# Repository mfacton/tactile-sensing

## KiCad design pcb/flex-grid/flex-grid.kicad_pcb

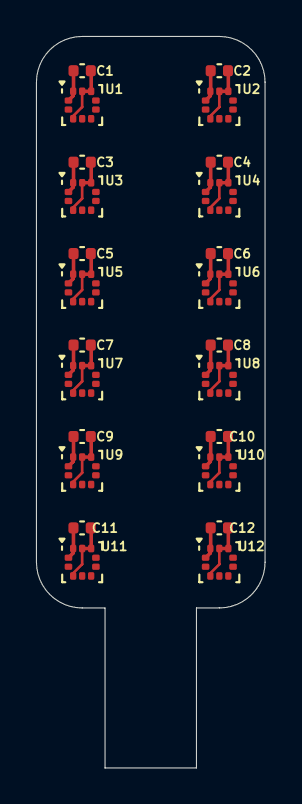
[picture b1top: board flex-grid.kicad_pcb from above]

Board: 2 copper layers, 12.7 x 40.6 mm, 24 parts (0 on the bottom side), 4 nets.

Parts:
C1, C2, C3, C4, C5, C6, C7, C8, C9, C10, C11, C12: 1u; C_0402_1005Metric
U1, U2, U3, U4, U5, U6, U7, U8, U9, U10, U11, U12: LPS22HB; ST_HLGA-10_2x2mm_P0.5mm_LayoutBorder3x2y

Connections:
/SCK: U1.2 (SCL), U2.2 (SCL), U3.2 (SCL), U4.2 (SCL), U5.2 (SCL), U6.2 (SCL), U7.2 (SCL), U8.2 (SCL), U9.2 (SCL), U10.2 (SCL), U11.2 (SCL), U12.2 (SCL)
/SDIO: U1.4 (SDA), U2.4 (SDA), U3.4 (SDA), U4.4 (SDA), U5.4 (SDA), U6.4 (SDA), U7.4 (SDA), U8.4 (SDA), U9.4 (SDA), U10.4 (SDA), U11.4 (SDA), U12.4 (SDA)
GND: C1.2, C2.2, C3.2, C4.2, C5.2, C6.2, C7.2, C8.2, C9.2, C10.2, C11.2, C12.2, U1.3 (RES), U1.8 (GND), U1.9 (GND), U2.3 (RES), U2.8 (GND), U2.9 (GND), U3.3 (RES), U3.8 (GND), U3.9 (GND), U4.3 (RES), U4.8 (GND), U4.9 (GND), U5.3 (RES), U5.8 (GND), U5.9 (GND), U6.3 (RES), U6.8 (GND), U6.9 (GND), U7.3 (RES), U7.8 (GND), U7.9 (GND), U8.3 (RES), U8.8 (GND), U8.9 (GND), U9.3 (RES), U9.8 (GND), U9.9 (GND), U10.3 (RES), U10.8 (GND), U10.9 (GND), U11.3 (RES), U11.8 (GND), U11.9 (GND), U12.3 (RES), U12.8 (GND), U12.9 (GND)
VDD: C1.1, C2.1, C3.1, C4.1, C5.1, C6.1, C7.1, C8.1, C9.1, C10.1, C11.1, C12.1, U1.1 (Vdd_IO), U1.10 (VDD), U2.1 (Vdd_IO), U2.10 (VDD), U3.1 (Vdd_IO), U3.10 (VDD), U4.1 (Vdd_IO), U4.10 (VDD), U5.1 (Vdd_IO), U5.10 (VDD), U6.1 (Vdd_IO), U6.10 (VDD), U7.1 (Vdd_IO), U7.10 (VDD), U8.1 (Vdd_IO), U8.10 (VDD), U9.1 (Vdd_IO), U9.10 (VDD), U10.1 (Vdd_IO), U10.10 (VDD), U11.1 (Vdd_IO), U11.10 (VDD), U12.1 (Vdd_IO), U12.10 (VDD)

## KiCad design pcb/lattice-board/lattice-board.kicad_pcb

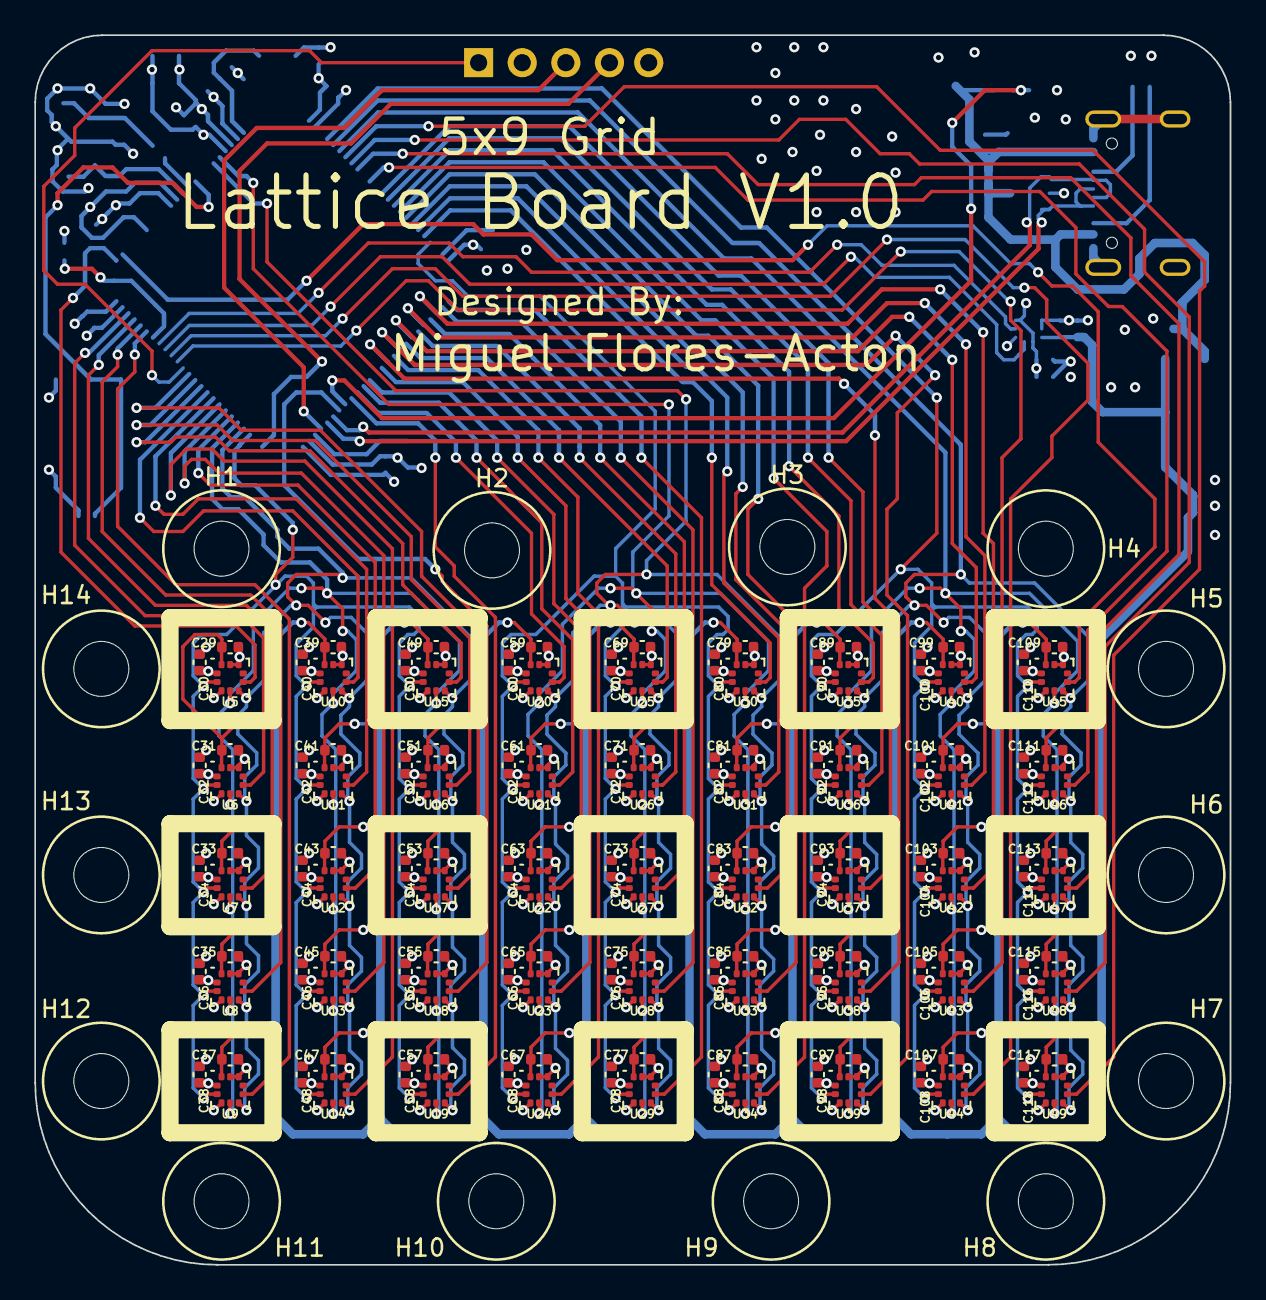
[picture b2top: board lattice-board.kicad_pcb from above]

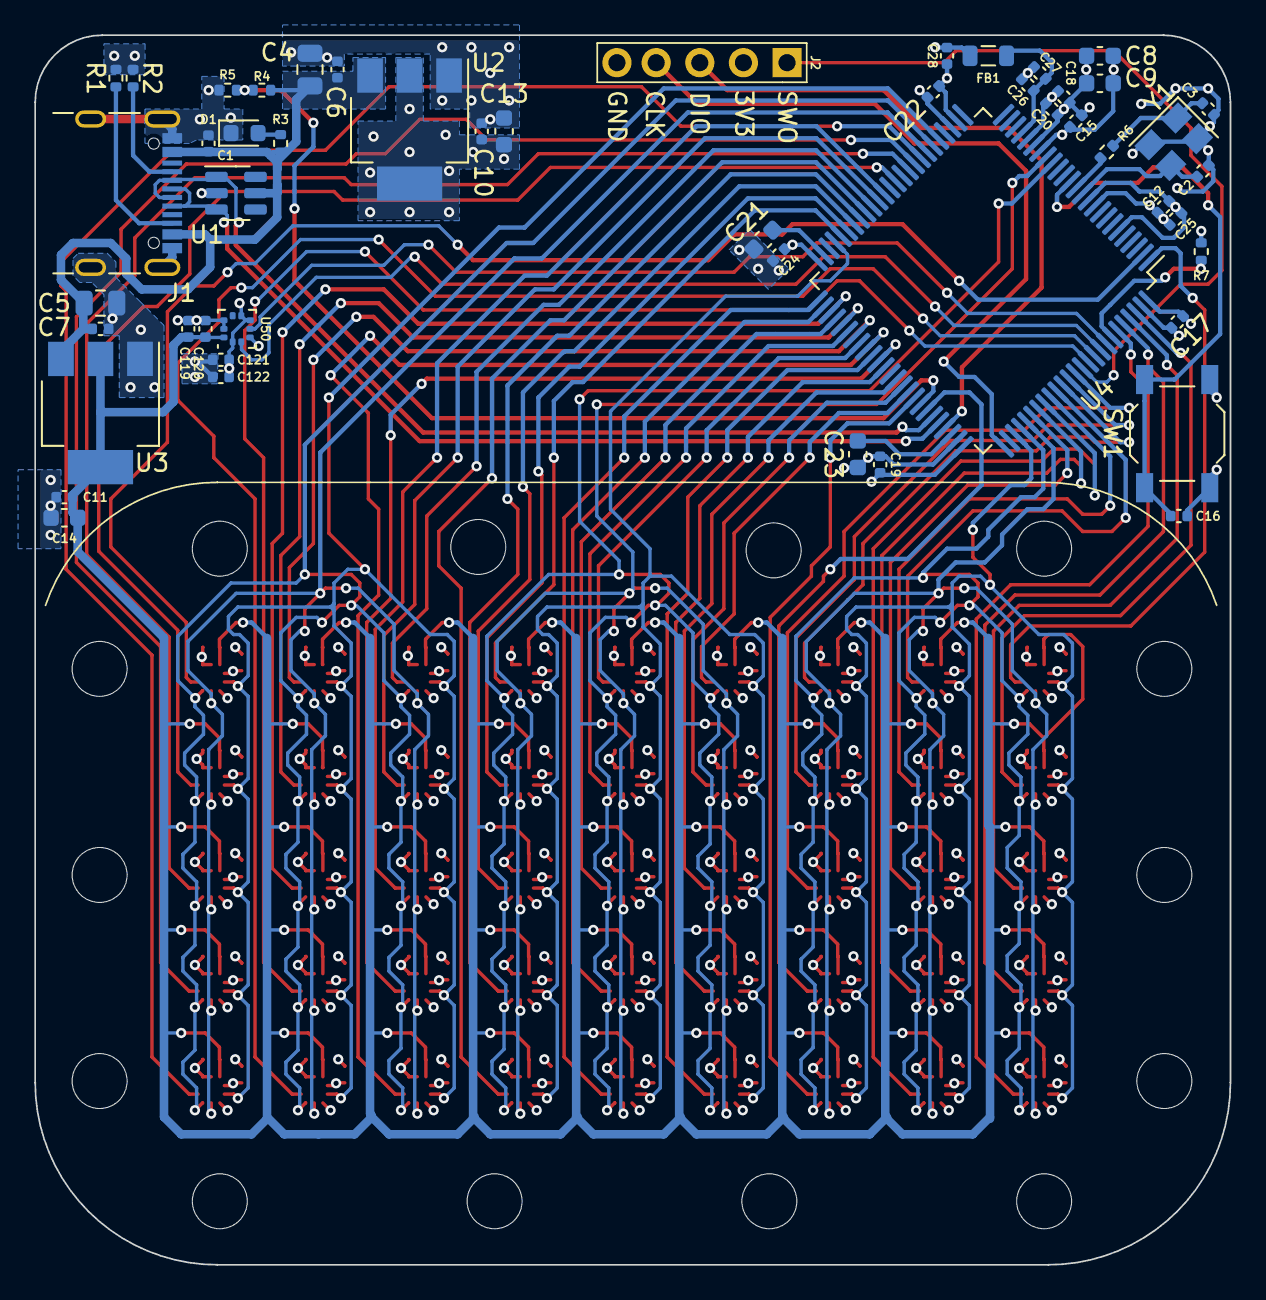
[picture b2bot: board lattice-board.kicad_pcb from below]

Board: 4 copper layers, 69.6 x 71.6 mm, 199 parts (50 on the bottom side), 77 nets.

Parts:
C1, C18, C27, C28: 1u; C_0402_1005Metric
C2, C3: 10p; C_0402_1005Metric
C4, C5: 22u; C_0805_2012Metric
C6, C7, C10, C11, C12, C15, C16, C17, C19, C20, C22, C24, C25, C26, C29, C30, C31, C32, C33, C34, C35, C36, C37, C38, C39, C40, C41, C42, C43, C44, C45, C46, C47, C48, C49, C50, C51, C52, C53, C54, C55, C56, C57, C58, C59, C60, C61, C62, C63, C64, C65, C66, C67, C68, C69, C70, C71, C72, C73, C74, C75, C76, C77, C78, C79, C80, C81, C82, C83, C84, C85, C86, C87, C88, C89, C90, C91, C92, C93, C94, C95, C96, C97, C98, C99, C100, C101, C102, C103, C104, C105, C106, C107, C108, C109, C110, C111, C112, C113, C114, C115, C116, C117, C118, C120, C121: 100n; C_0402_1005Metric
C8, C9, C21, C23: 2.2u; C_0603_1608Metric
C13, C14: 22u; C_0603_1608Metric
C119, C122: 4u7; C_0402_1005Metric
D1: LED; LED_0603_1608Metric
FB1: FerriteBead; L_0805_2012Metric
H1, H2, H3, H4, H5, H6, H7, H8, H9, H10, H11, H12, H13, H14: MountingHole; MountingHole_3.2mm_M3
J1: USB_C_Receptacle_USB2.0; USB_C_Receptacle_GCT_USB4105-xx-A_16P_TopMnt_Horizontal
J2: Conn_01x05_Pin; Conn_Header_P5-2.54
R1, R2: 5k1; R_0402_1005Metric
R3, R6: 510; R_0402_1005Metric
R4, R5, R7: 10k; R_0402_1005Metric
SW1: SW_Push; SW_SPST_TL3342
U1: SRV05-4; SOT-23-6
U2, U3: AMS1117-3.3; SOT-223-3_TabPin2
U4: STM32F407VETx; LQFP-100_14x14mm_P0.5mm
U5, U6, U7, U8, U9, U10, U11, U12, U13, U14, U15, U16, U17, U18, U19, U20, U21, U22, U23, U24, U25, U26, U27, U28, U29, U30, U31, U32, U33, U34, U35, U36, U37, U38, U39, U40, U41, U42, U43, U44, U45, U46, U47, U48, U49, U50: LPS22HB; ST_HLGA-10_2x2mm_P0.5mm_LayoutBorder3x2y
Y1: 16MHz; Crystal_SMD_3225-4Pin_3.2x2.5mm

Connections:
+3.3VA: C26.1, C27.1, FB1.1, U4.22 (VDDA)
/BOOT0: R7.1, U4.94 (BOOT0)
/CSnA1: U4.1 (PE2), U5.6 (~CS)
/CSnA2: U4.98 (PE1), U6.6 (~CS)
/CSnA3: U4.97 (PE0), U7.6 (~CS)
/CSnA4: U4.96 (PB9), U8.6 (~CS)
/CSnA5: U4.95 (PB8), U9.6 (~CS)
/CSnA6: U4.85 (PD4), U10.6 (~CS)
/CSnA7: U4.84 (PD3), U11.6 (~CS)
/CSnA8: U4.81 (PD0), U12.6 (~CS)
/CSnA9: U4.82 (PD1), U13.6 (~CS)
/CSnA10: U4.83 (PD2), U14.6 (~CS)
/CSnA11: U4.86 (PD5), U15.6 (~CS)
/CSnA12: U4.87 (PD6), U16.6 (~CS)
/CSnA13: U4.88 (PD7), U17.6 (~CS)
/CSnA14: U4.69 (PA10), U18.6 (~CS)
/CSnA15: U4.67 (PA8), U19.6 (~CS)
/CSnB1: U4.66 (PC9), U20.6 (~CS)
/CSnB2: U4.65 (PC8), U21.6 (~CS)
/CSnB3: U4.64 (PC7), U22.6 (~CS)
/CSnB4: U4.62 (PD15), U23.6 (~CS)
/CSnB5: U4.60 (PD13), U24.6 (~CS)
/CSnB6: U4.58 (PD11), U25.6 (~CS)
/CSnB7: U4.56 (PD9), U26.6 (~CS)
/CSnB8: U4.54 (PB15), U27.6 (~CS)
/CSnB9: U4.52 (PB13), U28.6 (~CS)
/CSnB10: U4.51 (PB12), U29.6 (~CS)
/CSnB11: U4.46 (PE15), U30.6 (~CS)
/CSnB12: U4.45 (PE14), U31.6 (~CS)
/CSnB13: U4.44 (PE13), U32.6 (~CS)
/CSnB14: U4.43 (PE12), U33.6 (~CS)
/CSnB15: U4.42 (PE11), U34.6 (~CS)
/CSnC1: U4.41 (PE10), U35.6 (~CS)
/CSnC2: U4.40 (PE9), U36.6 (~CS)
/CSnC3: U4.39 (PE8), U37.6 (~CS)
/CSnC4: U4.61 (PD14), U38.6 (~CS)
/CSnC5: U4.59 (PD12), U39.6 (~CS)
/CSnC6: U4.57 (PD10), U40.6 (~CS)
/CSnC7: U4.55 (PD8), U41.6 (~CS)
/CSnC8: U4.53 (PB14), U42.6 (~CS)
/CSnC9: U4.90 (PB4), U43.6 (~CS)
/CSnC10: U4.91 (PB5), U44.6 (~CS)
/CSnC11: U4.2 (PE3), U45.6 (~CS)
/CSnC12: U4.37 (PB2), U46.6 (~CS)
/CSnC13: U4.35 (PB0), U47.6 (~CS)
/CSnC14: U4.34 (PC5), U48.6 (~CS)
/CSnC15: U4.33 (PC4), U49.6 (~CS)
/NRST: C16.1, SW1.1, U4.14 (NRST)
/OSCIN: C2.2, U4.12 (PH0), Y1.3
/OSCLO: C3.2, R6.1, Y1.1
/OSCOUT: R6.2, U4.13 (PH1)
/SCKA: U4.78 (PC10), U5.2 (SCL), U6.2 (SCL), U7.2 (SCL), U8.2 (SCL), U9.2 (SCL), U10.2 (SCL), U11.2 (SCL), U12.2 (SCL), U13.2 (SCL), U14.2 (SCL), U15.2 (SCL), U16.2 (SCL), U17.2 (SCL), U18.2 (SCL), U19.2 (SCL)
/SCKB: U4.47 (PB10), U20.2 (SCL), U21.2 (SCL), U22.2 (SCL), U23.2 (SCL), U24.2 (SCL), U25.2 (SCL), U26.2 (SCL), U27.2 (SCL), U28.2 (SCL), U29.2 (SCL), U30.2 (SCL), U31.2 (SCL), U32.2 (SCL), U33.2 (SCL), U34.2 (SCL)
/SCKC: U4.30 (PA5), U35.2 (SCL), U36.2 (SCL), U37.2 (SCL), U38.2 (SCL), U39.2 (SCL), U40.2 (SCL), U41.2 (SCL), U42.2 (SCL), U43.2 (SCL), U44.2 (SCL), U45.2 (SCL), U46.2 (SCL), U47.2 (SCL), U48.2 (SCL), U49.2 (SCL)
/SCL1: U4.92 (PB6), U50.2 (SCL)
/SDA1: U4.93 (PB7), U50.4 (SDA)
/SDIA: U4.80 (PC12), U5.4 (SDA), U6.4 (SDA), U7.4 (SDA), U8.4 (SDA), U9.4 (SDA), U10.4 (SDA), U11.4 (SDA), U12.4 (SDA), U13.4 (SDA), U14.4 (SDA), U15.4 (SDA), U16.4 (SDA), U17.4 (SDA), U18.4 (SDA), U19.4 (SDA)
/SDIB: U4.18 (PC3), U20.4 (SDA), U21.4 (SDA), U22.4 (SDA), U23.4 (SDA), U24.4 (SDA), U25.4 (SDA), U26.4 (SDA), U27.4 (SDA), U28.4 (SDA), U29.4 (SDA), U30.4 (SDA), U31.4 (SDA), U32.4 (SDA), U33.4 (SDA), U34.4 (SDA)
/SDIC: U4.32 (PA7), U35.4 (SDA), U36.4 (SDA), U37.4 (SDA), U38.4 (SDA), U39.4 (SDA), U40.4 (SDA), U41.4 (SDA), U42.4 (SDA), U43.4 (SDA), U44.4 (SDA), U45.4 (SDA), U46.4 (SDA), U47.4 (SDA), U48.4 (SDA), U49.4 (SDA)
/SDOA: U4.79 (PC11), U5.5 (SA0), U6.5 (SA0), U7.5 (SA0), U8.5 (SA0), U9.5 (SA0), U10.5 (SA0), U11.5 (SA0), U12.5 (SA0), U13.5 (SA0), U14.5 (SA0), U15.5 (SA0), U16.5 (SA0), U17.5 (SA0), U18.5 (SA0), U19.5 (SA0)
/SDOB: U4.17 (PC2), U20.5 (SA0), U21.5 (SA0), U22.5 (SA0), U23.5 (SA0), U24.5 (SA0), U25.5 (SA0), U26.5 (SA0), U27.5 (SA0), U28.5 (SA0), U29.5 (SA0), U30.5 (SA0), U31.5 (SA0), U32.5 (SA0), U33.5 (SA0), U34.5 (SA0)
/SDOC: U4.31 (PA6), U35.5 (SA0), U36.5 (SA0), U37.5 (SA0), U38.5 (SA0), U39.5 (SA0), U40.5 (SA0), U41.5 (SA0), U42.5 (SA0), U43.5 (SA0), U44.5 (SA0), U45.5 (SA0), U46.5 (SA0), U47.5 (SA0), U48.5 (SA0), U49.5 (SA0)
/SNSBUS: R4.2, R5.1, U4.68 (PA9)
/SWCLK: J2.4, U4.76 (PA14)
/SWDIO: J2.3, U4.72 (PA13)
/SWO: J2.1, U4.89 (PB3)
/USB_D+: J1.A6 (D+), J1.B6 (D+), U1.3 (IO2), U4.71 (PA12)
/USB_D-: J1.A7 (D-), J1.B7 (D-), U1.1 (IO1), U4.70 (PA11)
/VBLED: D1.2 (A), R3.2
/VCAP1: C21.1, U4.49 (VCAP_1)
/VCAP2: C23.1, U4.73 (VCAP_2)
GND: C1.2, C2.1, C3.1, C4.2, C5.2, C6.2, C7.2, C8.2, C9.2, C10.2, C11.2, C12.2, C13.2, C14.2, C15.2, C16.2, C17.2, C18.2, C19.2, C20.2, C21.2, C22.2, C23.2, C24.2, C25.2, C26.2, C27.2, C28.2, C29.2, C30.2, C31.2, C32.2, C33.2, C34.2, C35.2, C36.2, C37.2, C38.2, C39.2, C40.2, C41.2, C42.2, C43.2, C44.2, C45.2, C46.2, C47.2, C48.2, C49.2, C50.2, C51.2, C52.2, C53.2, C54.2, C55.2, C56.2, C57.2, C58.2, C59.2, C60.2, C61.2, C62.2, C63.2, C64.2, C65.2, C66.2, C67.2, C68.2, C69.2, C70.2, C71.2, C72.2, C73.2, C74.2, C75.2, C76.2, C77.2, C78.2, C79.2, C80.2, C81.2, C82.2, C83.2, C84.2, C85.2, C86.2, C87.2, C88.2, C89.2, C90.2, C91.2, C92.2, C93.2, C94.2, C95.2, C96.2, C97.2, C98.2, C99.2, C100.2, C101.2, C102.2, C103.2, C104.2, C105.2, C106.2, C107.2, C108.2, C109.2, C110.2, C111.2, C112.2, C113.2, C114.2, C115.2, C116.2, C117.2, C118.2, C119.2, C120.2, C121.2, C122.2, D1.1 (K), J1.A1 (GND), J1.A12 (GND), J1.B1 (GND), J1.B12 (GND), J1.S1 (SHIELD), J2.5, R1.2, R2.2, R5.2, R7.2, SW1.2, U1.2 (VN), U2.1 (GND), U3.1 (GND), U4.10 (VSS), U4.20 (VSSA), U4.27 (VSS), U4.74 (VSS), U4.99 (VSS), U5.3 (RES), U5.8 (GND), U5.9 (GND), U6.3 (RES), U6.8 (GND), U6.9 (GND), U7.3 (RES), U7.8 (GND), U7.9 (GND), U8.3 (RES), U8.8 (GND), U8.9 (GND), U9.3 (RES), U9.8 (GND), U9.9 (GND), U10.3 (RES), U10.8 (GND), U10.9 (GND), U11.3 (RES), U11.8 (GND), U11.9 (GND), U12.3 (RES), U12.8 (GND), U12.9 (GND), U13.3 (RES), U13.8 (GND), U13.9 (GND), U14.3 (RES), U14.8 (GND), U14.9 (GND), U15.3 (RES), U15.8 (GND), U15.9 (GND), U16.3 (RES), U16.8 (GND), U16.9 (GND), U17.3 (RES), U17.8 (GND), U17.9 (GND), U18.3 (RES), U18.8 (GND), U18.9 (GND), U19.3 (RES), U19.8 (GND), U19.9 (GND), U20.3 (RES), U20.8 (GND), U20.9 (GND), U21.3 (RES), U21.8 (GND), U21.9 (GND), U22.3 (RES), U22.8 (GND), U22.9 (GND), U23.3 (RES), U23.8 (GND), U23.9 (GND), U24.3 (RES), U24.8 (GND), U24.9 (GND), U25.3 (RES), U25.8 (GND), U25.9 (GND), U26.3 (RES), U26.8 (GND), U26.9 (GND), U27.3 (RES), U27.8 (GND), U27.9 (GND), U28.3 (RES), U28.8 (GND), U28.9 (GND), U29.3 (RES), U29.8 (GND), U29.9 (GND), U30.3 (RES), U30.8 (GND), U30.9 (GND), U31.3 (RES), U31.8 (GND), U31.9 (GND), U32.3 (RES), U32.8 (GND), U32.9 (GND), U33.3 (RES), U33.8 (GND), U33.9 (GND), U34.3 (RES), U34.8 (GND), U34.9 (GND), U35.3 (RES), U35.8 (GND), U35.9 (GND), U36.3 (RES), U36.8 (GND), U36.9 (GND), U37.3 (RES), U37.8 (GND), U37.9 (GND), U38.3 (RES), U38.8 (GND), U38.9 (GND), U39.3 (RES), U39.8 (GND), U39.9 (GND), U40.3 (RES), U40.8 (GND), U40.9 (GND), U41.3 (RES), U41.8 (GND), U41.9 (GND), U42.3 (RES), U42.8 (GND), U42.9 (GND), U43.3 (RES), U43.8 (GND), U43.9 (GND), U44.3 (RES), U44.8 (GND), U44.9 (GND), U45.3 (RES), U45.8 (GND), U45.9 (GND), U46.3 (RES), U46.8 (GND), U46.9 (GND), U47.3 (RES), U47.8 (GND), U47.9 (GND), U48.3 (RES), U48.8 (GND), U48.9 (GND), U49.3 (RES), U49.8 (GND), U49.9 (GND), U50.3 (RES), U50.8 (GND), U50.9 (GND), Y1.2, Y1.4
unnamed: J1.A5 (CC1), R2.1
unnamed: J1.B5 (CC2), R1.1
VBUS: C1.1, C4.1, C5.1, C6.1, C7.1, J1.A4 (VBUS), J1.A9 (VBUS), J1.B4 (VBUS), J1.B9 (VBUS), R3.1, R4.1, U1.5 (VP), U2.3 (VI), U3.3 (VI)
VDD: C8.1, C9.1, C10.1, C12.1, C13.1, C15.1, C17.1, C18.1, C19.1, C20.1, C22.1, C24.1, C25.1, C28.1, C30.1, C32.1, C34.1, C36.1, C38.1, C40.1, C42.1, C44.1, C46.1, C48.1, C50.1, C52.1, C54.1, C56.1, C58.1, C60.1, C62.1, C64.1, C66.1, C68.1, C70.1, C72.1, C74.1, C76.1, C78.1, C80.1, C82.1, C84.1, C86.1, C88.1, C90.1, C92.1, C94.1, C96.1, C98.1, C100.1, C102.1, C104.1, C106.1, C108.1, C110.1, C112.1, C114.1, C116.1, C118.1, C121.1, C122.1, FB1.2, J2.2, U2.2 (VO), U4.6 (VBAT), U4.11 (VDD), U4.19 (VDD), U4.21 (VREF+), U4.28 (VDD), U4.50 (VDD), U4.75 (VDD), U4.100 (VDD), U5.1 (Vdd_IO), U6.1 (Vdd_IO), U7.1 (Vdd_IO), U8.1 (Vdd_IO), U9.1 (Vdd_IO), U10.1 (Vdd_IO), U11.1 (Vdd_IO), U12.1 (Vdd_IO), U13.1 (Vdd_IO), U14.1 (Vdd_IO), U15.1 (Vdd_IO), U16.1 (Vdd_IO), U17.1 (Vdd_IO), U18.1 (Vdd_IO), U19.1 (Vdd_IO), U20.1 (Vdd_IO), U21.1 (Vdd_IO), U22.1 (Vdd_IO), U23.1 (Vdd_IO), U24.1 (Vdd_IO), U25.1 (Vdd_IO), U26.1 (Vdd_IO), U27.1 (Vdd_IO), U28.1 (Vdd_IO), U29.1 (Vdd_IO), U30.1 (Vdd_IO), U31.1 (Vdd_IO), U32.1 (Vdd_IO), U33.1 (Vdd_IO), U34.1 (Vdd_IO), U35.1 (Vdd_IO), U36.1 (Vdd_IO), U37.1 (Vdd_IO), U38.1 (Vdd_IO), U39.1 (Vdd_IO), U40.1 (Vdd_IO), U41.1 (Vdd_IO), U42.1 (Vdd_IO), U43.1 (Vdd_IO), U44.1 (Vdd_IO), U45.1 (Vdd_IO), U46.1 (Vdd_IO), U47.1 (Vdd_IO), U48.1 (Vdd_IO), U49.1 (Vdd_IO), U50.1 (Vdd_IO), U50.5 (SA0), U50.6 (~CS)
VDDA: C11.1, C14.1, C29.1, C31.1, C33.1, C35.1, C37.1, C39.1, C41.1, C43.1, C45.1, C47.1, C49.1, C51.1, C53.1, C55.1, C57.1, C59.1, C61.1, C63.1, C65.1, C67.1, C69.1, C71.1, C73.1, C75.1, C77.1, C79.1, C81.1, C83.1, C85.1, C87.1, C89.1, C91.1, C93.1, C95.1, C97.1, C99.1, C101.1, C103.1, C105.1, C107.1, C109.1, C111.1, C113.1, C115.1, C117.1, C119.1, C120.1, U3.2 (VO), U5.10 (VDD), U6.10 (VDD), U7.10 (VDD), U8.10 (VDD), U9.10 (VDD), U10.10 (VDD), U11.10 (VDD), U12.10 (VDD), U13.10 (VDD), U14.10 (VDD), U15.10 (VDD), U16.10 (VDD), U17.10 (VDD), U18.10 (VDD), U19.10 (VDD), U20.10 (VDD), U21.10 (VDD), U22.10 (VDD), U23.10 (VDD), U24.10 (VDD), U25.10 (VDD), U26.10 (VDD), U27.10 (VDD), U28.10 (VDD), U29.10 (VDD), U30.10 (VDD), U31.10 (VDD), U32.10 (VDD), U33.10 (VDD), U34.10 (VDD), U35.10 (VDD), U36.10 (VDD), U37.10 (VDD), U38.10 (VDD), U39.10 (VDD), U40.10 (VDD), U41.10 (VDD), U42.10 (VDD), U43.10 (VDD), U44.10 (VDD), U45.10 (VDD), U46.10 (VDD), U47.10 (VDD), U48.10 (VDD), U49.10 (VDD), U50.10 (VDD)

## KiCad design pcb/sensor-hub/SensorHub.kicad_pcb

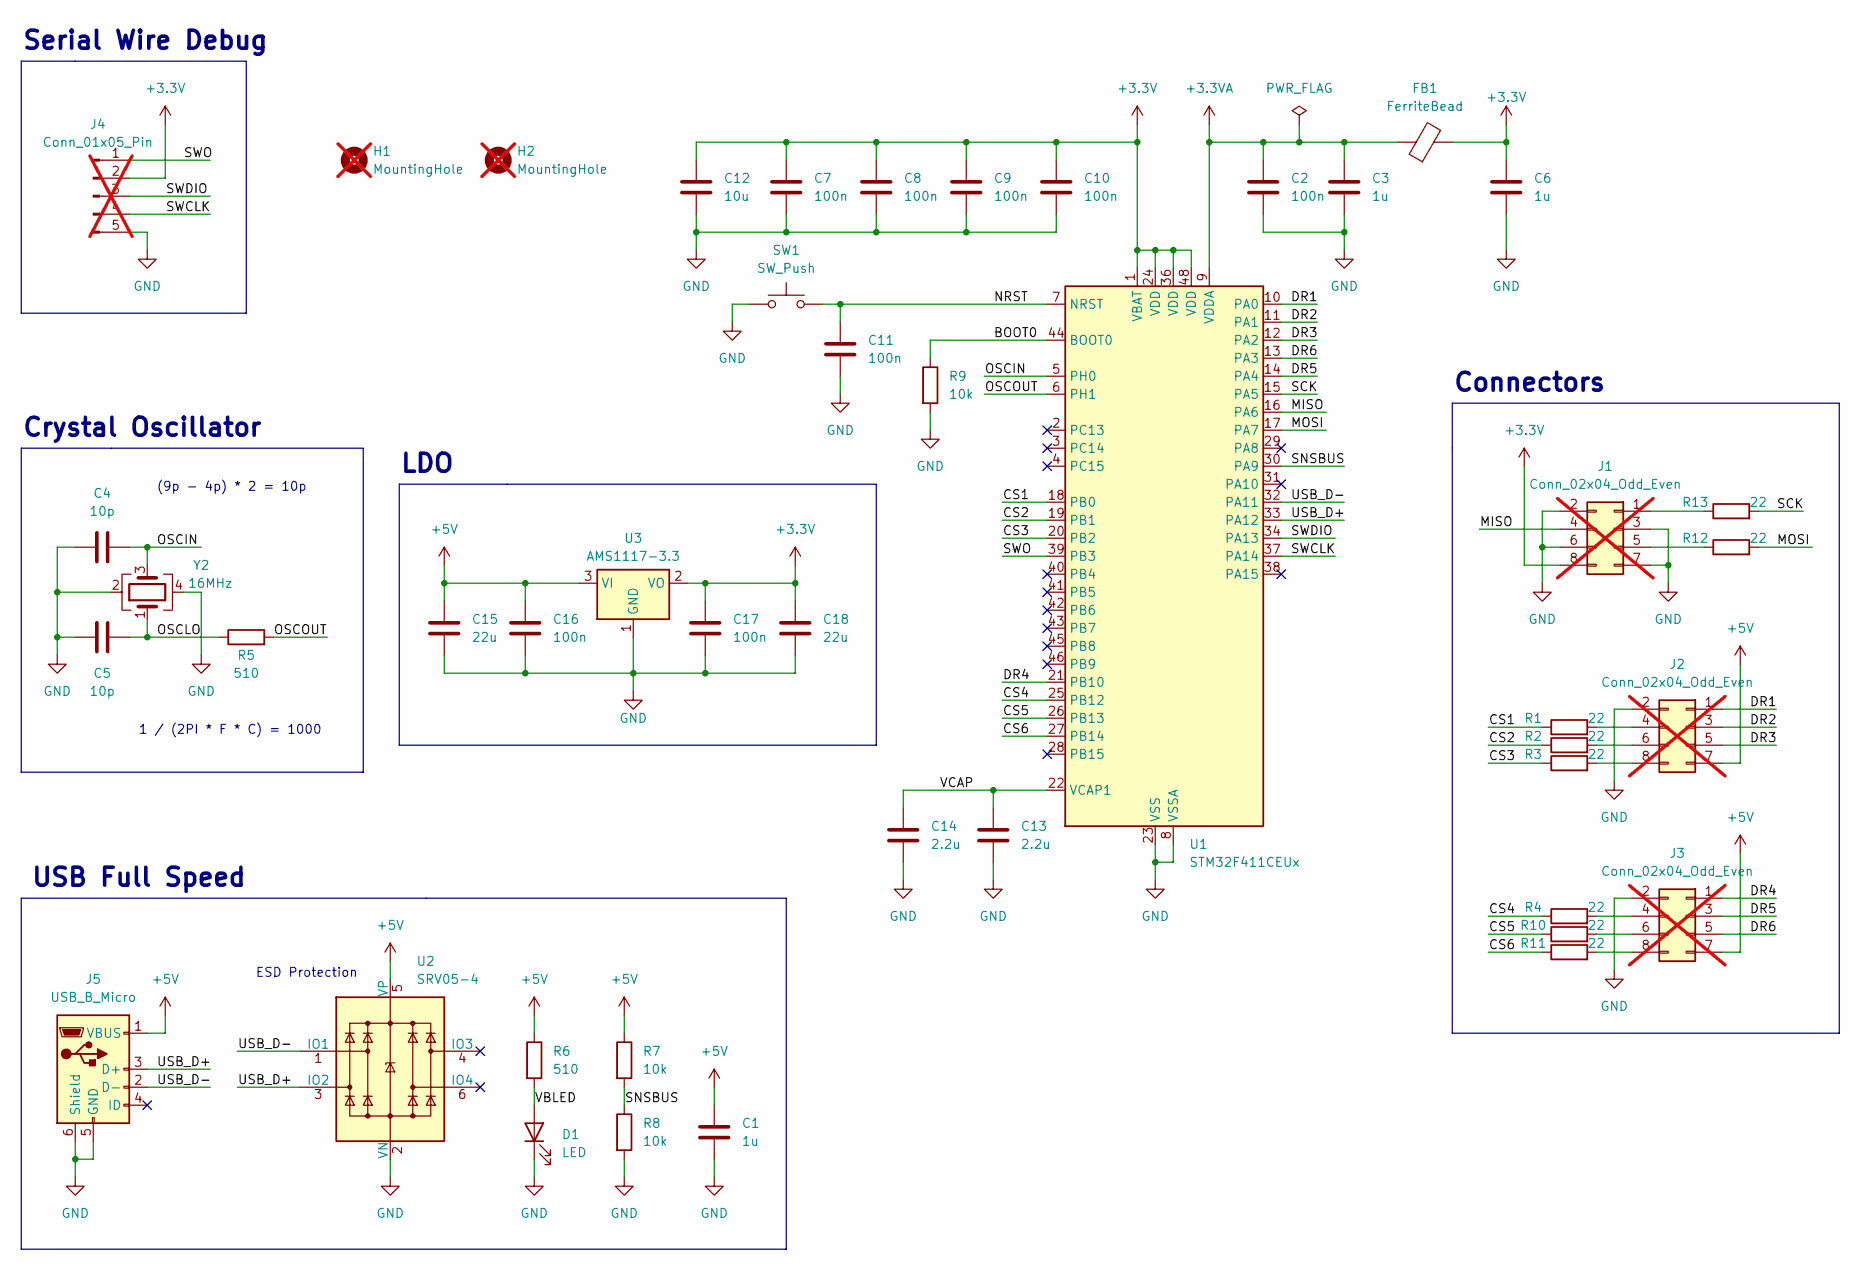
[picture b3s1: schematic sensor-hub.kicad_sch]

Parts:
C1, C3, C6: 1u; C_0402_1005Metric
C2, C7, C8, C9, C10, C11, C16, C17: 100n; C_0402_1005Metric
C4, C5: 10p; C_0402_1005Metric
C12: 10u; C_0603_1608Metric
C13, C14: 2.2u; C_0402_1005Metric
C15: 22u; C_0805_2012Metric
C18: 22u; C_0603_1608Metric
D1: LED; LED_0603_1608Metric
FB1: FerriteBead; L_0805_2012Metric; LCSC C32375
H1, H2: MountingHole; MountingHole_3.2mm_M3; not fitted
J1, J2, J3: Conn_02x04_Odd_Even; PinHeader_2x04_P2.54mm_Vertical; not fitted
J4: Conn_01x05_Pin; Conn_Header_P5-2.54; not fitted
J5: USB_B_Micro; USB_Micro-B_Molex-105017-0001; LCSC C668587
R1, R2, R3, R4, R10, R11, R12, R13: 22; R_0402_1005Metric
R5, R6: 510; R_0402_1005Metric
R7, R8, R9: 10k; R_0402_1005Metric
SW1: SW_Push; SW_SPST_TL3342
U1: STM32F411CEUx; QFN-48-1EP_7x7mm_P0.5mm_EP5.6x5.6mm; LCSC C60420
U2: SRV05-4; SOT-23-6; LCSC C7420376
U3: AMS1117-3.3; SOT-223-3_TabPin2; LCSC C6186
Y2: 16MHz; Crystal_SMD_3225-4Pin_3.2x2.5mm

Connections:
+3.3V: C6.1, C7.1, C8.1, C9.1, C10.1, C12.1, C17.1, C18.1, FB1.2, J1.8, J4.2, U1.1 (VBAT), U1.24 (VDD), U1.36 (VDD), U1.48 (VDD), U3.2 (VO)
+3.3VA: C2.1, C3.1, FB1.1, U1.9 (VDDA)
+5V: C1.1, C15.1, C16.1, J2.7, J3.7, J5.1 (VBUS), R6.1, R7.1, U2.5 (VP), U3.3 (VI)
/BOOT0: R9.1, U1.44 (BOOT0)
/CS1: R1.1, U1.18 (PB0)
/CS2: R2.1, U1.19 (PB1)
/CS3: R3.1, U1.20 (PB2)
/CS4: R4.1, U1.25 (PB12)
/CS5: R10.1, U1.26 (PB13)
/CS6: R11.1, U1.27 (PB14)
/DR1: J2.1, U1.10 (PA0)
/DR2: J2.3, U1.11 (PA1)
/DR3: J2.5, U1.12 (PA2)
/DR4: J3.1, U1.21 (PB10)
/DR5: J3.3, U1.14 (PA4)
/DR6: J3.5, U1.13 (PA3)
/MISO: J1.4, U1.16 (PA6)
/MOSI: R12.2, U1.17 (PA7)
/NRST: C11.1, SW1.1, U1.7 (NRST)
/OSCIN: C4.2, U1.5 (PH0), Y2.3
/OSCLO: C5.2, R5.1, Y2.1
/OSCOUT: R5.2, U1.6 (PH1)
/SCK: R13.2, U1.15 (PA5)
/SNSBUS: R7.2, R8.1, U1.30 (PA9)
/SWCLK: J4.4, U1.37 (PA14)
/SWDIO: J4.3, U1.34 (PA13)
/SWO: J4.1, U1.39 (PB3)
/USB_D+: J5.3 (D+), U1.33 (PA12), U2.3 (IO2)
/USB_D-: J5.2 (D-), U1.32 (PA11), U2.1 (IO1)
/VBLED: D1.2 (A), R6.2
/VCAP: C13.1, C14.1, U1.22 (VCAP1)
GND: C1.2, C2.2, C3.2, C4.1, C5.1, C6.2, C7.2, C8.2, C9.2, C10.2, C11.2, C12.2, C13.2, C14.2, C15.2, C16.2, C17.2, C18.2, D1.1 (K), J1.2, J1.3, J1.6, J1.7, J2.2, J3.2, J4.5, J5.5 (GND), J5.6 (Shield), R8.2, R9.2, SW1.2, U1.8 (VSSA), U1.23 (VSS), U1.35 (VSS), U1.47 (VSS), U1.49 (VSS), U2.2 (VN), U3.1 (GND), Y2.2, Y2.4
unnamed: J1.1, R13.1
unnamed: J1.5, R12.1
unnamed: J2.4, R1.2
unnamed: J2.6, R2.2
unnamed: J2.8, R3.2
unnamed: J3.4, R4.2
unnamed: J3.6, R10.2
unnamed: J3.8, R11.2

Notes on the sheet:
USB Full Speed
Connectors
ESD Protection
1 / (2PI * F * C) = 1000
Serial Wire Debug
LDO
Crystal Oscillator
(9p - 4p) * 2 = 10p

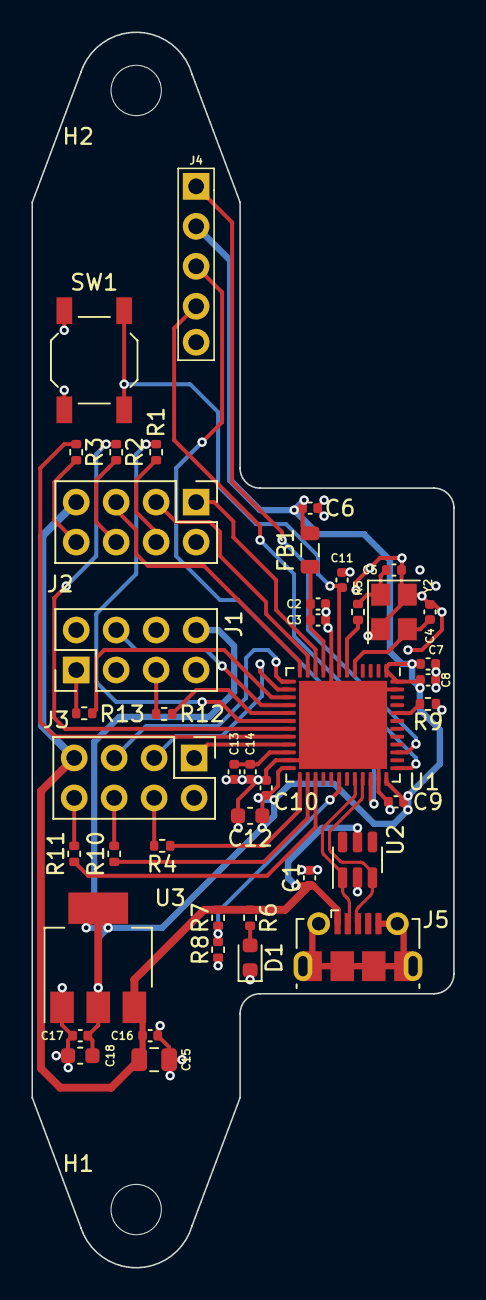
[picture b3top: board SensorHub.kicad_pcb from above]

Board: 4 copper layers, 26.8 x 78.5 mm, 45 parts (0 on the bottom side), 40 nets.

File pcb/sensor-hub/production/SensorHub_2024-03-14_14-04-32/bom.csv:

Designator,Footprint,Quantity,Value,LCSC Part #
"C1, C3, C6",0402,3,1u,
"C10, C11, C16, C17, C2, C7, C8, C9",0402,8,100n,
C12,0603,1,10u,
"C13, C14",0402,2,2.2u,
C15,0805,1,22u,
C18,0603,1,22u,
"C4, C5",0402,2,10p,
D1,0603,1,LED,
FB1,0805,1,FerriteBead,C32375
J5,USB_Micro-B_Molex-105017-0001,1,USB_B_Micro,
"R1, R10, R11, R12, R13, R2, R3, R4",0402,8,22,
"R5, R6",0402,2,510,
"R7, R8, R9",0402,3,10k,
SW1,SW_SPST_TL3342,1,SW_Push,
U1,QFN-48-1EP_7x7mm_P0.5mm_EP5.6x5.6mm,1,STM32F411CEUx,C60420
U2,SOT-23-6,1,SRV05-4,C7420376
U3,SOT-223-3_TabPin2,1,AMS1117-3.3,C6186
Y2,Crystal_SMD_3225-4Pin_3.2x2.5mm,1,16MHz,
